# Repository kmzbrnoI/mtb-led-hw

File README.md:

MTB-LED PCB
===========

MTB-LED is a 32-output LED driver. It communicates over [MTBbus](https://mtb.kmz-brno.cz/bus) (RS485).
The module is designed for controlling street and house lights on model
railroad, however is could be used generally in any other application.

This repository contains schematics & PCB layout of MTB-LED PCB. Firmware
for main MCU ATmega328p is available
[here](https://github.com/kmzbrnoI/mtb-led-fw). More information about
MTB in available [here](https://mtb.kmz-brno.cz/).

## Design

Schematics & PCB are designed in KiCad 9.

## Production

PCB is prepared to be automatically assembled in [JLCPCB](https://jlcpcb.com/).
SMD parts on **bootom** side should be assembled. Each SMD part has its `LCSC`
attribute set.

```bash
$ make
```

## Parameters

 * Input voltage: 7–17 V.
   Protection: when > 18 V is applied, input is shorted. Afterwards, current
   is limited by PTC fuse on input to 200 mA. Reverse-polarity protection.
 * Max current consumption: ??? mA.
 * Outputs: 32 constant-current PWM-controlled outputs for LED connection. Connect
   positive pole of LED to power supply, negative to the MTB-LED module.

## Piece check

Following checks should be performed to mark each manufactured piece as *QC PASS*.

1. Check module communicates on MTBbus.
2. Check all LEDs are working.
3. Check button is working.
4. Calibrate `TS_OFFSET`, check diagnostic including temperature measurement is working.
5. Check all outputs are working.

## Authors

MTB-LED v4 module is designed by [Jan Malina](mailto:jan.malina@kmz-brno.cz),
[Model Railway Club Brno](https://www.kmz-brno.cz/).

## License

Content of the repository is provided under [Creative Commons
Attribution-ShareAlike 4.0
License](https://creativecommons.org/licenses/by-sa/4.0/) as openhardware
project. You may download any data, contribute to the project, create PCB
yourself or even sell it yourself.

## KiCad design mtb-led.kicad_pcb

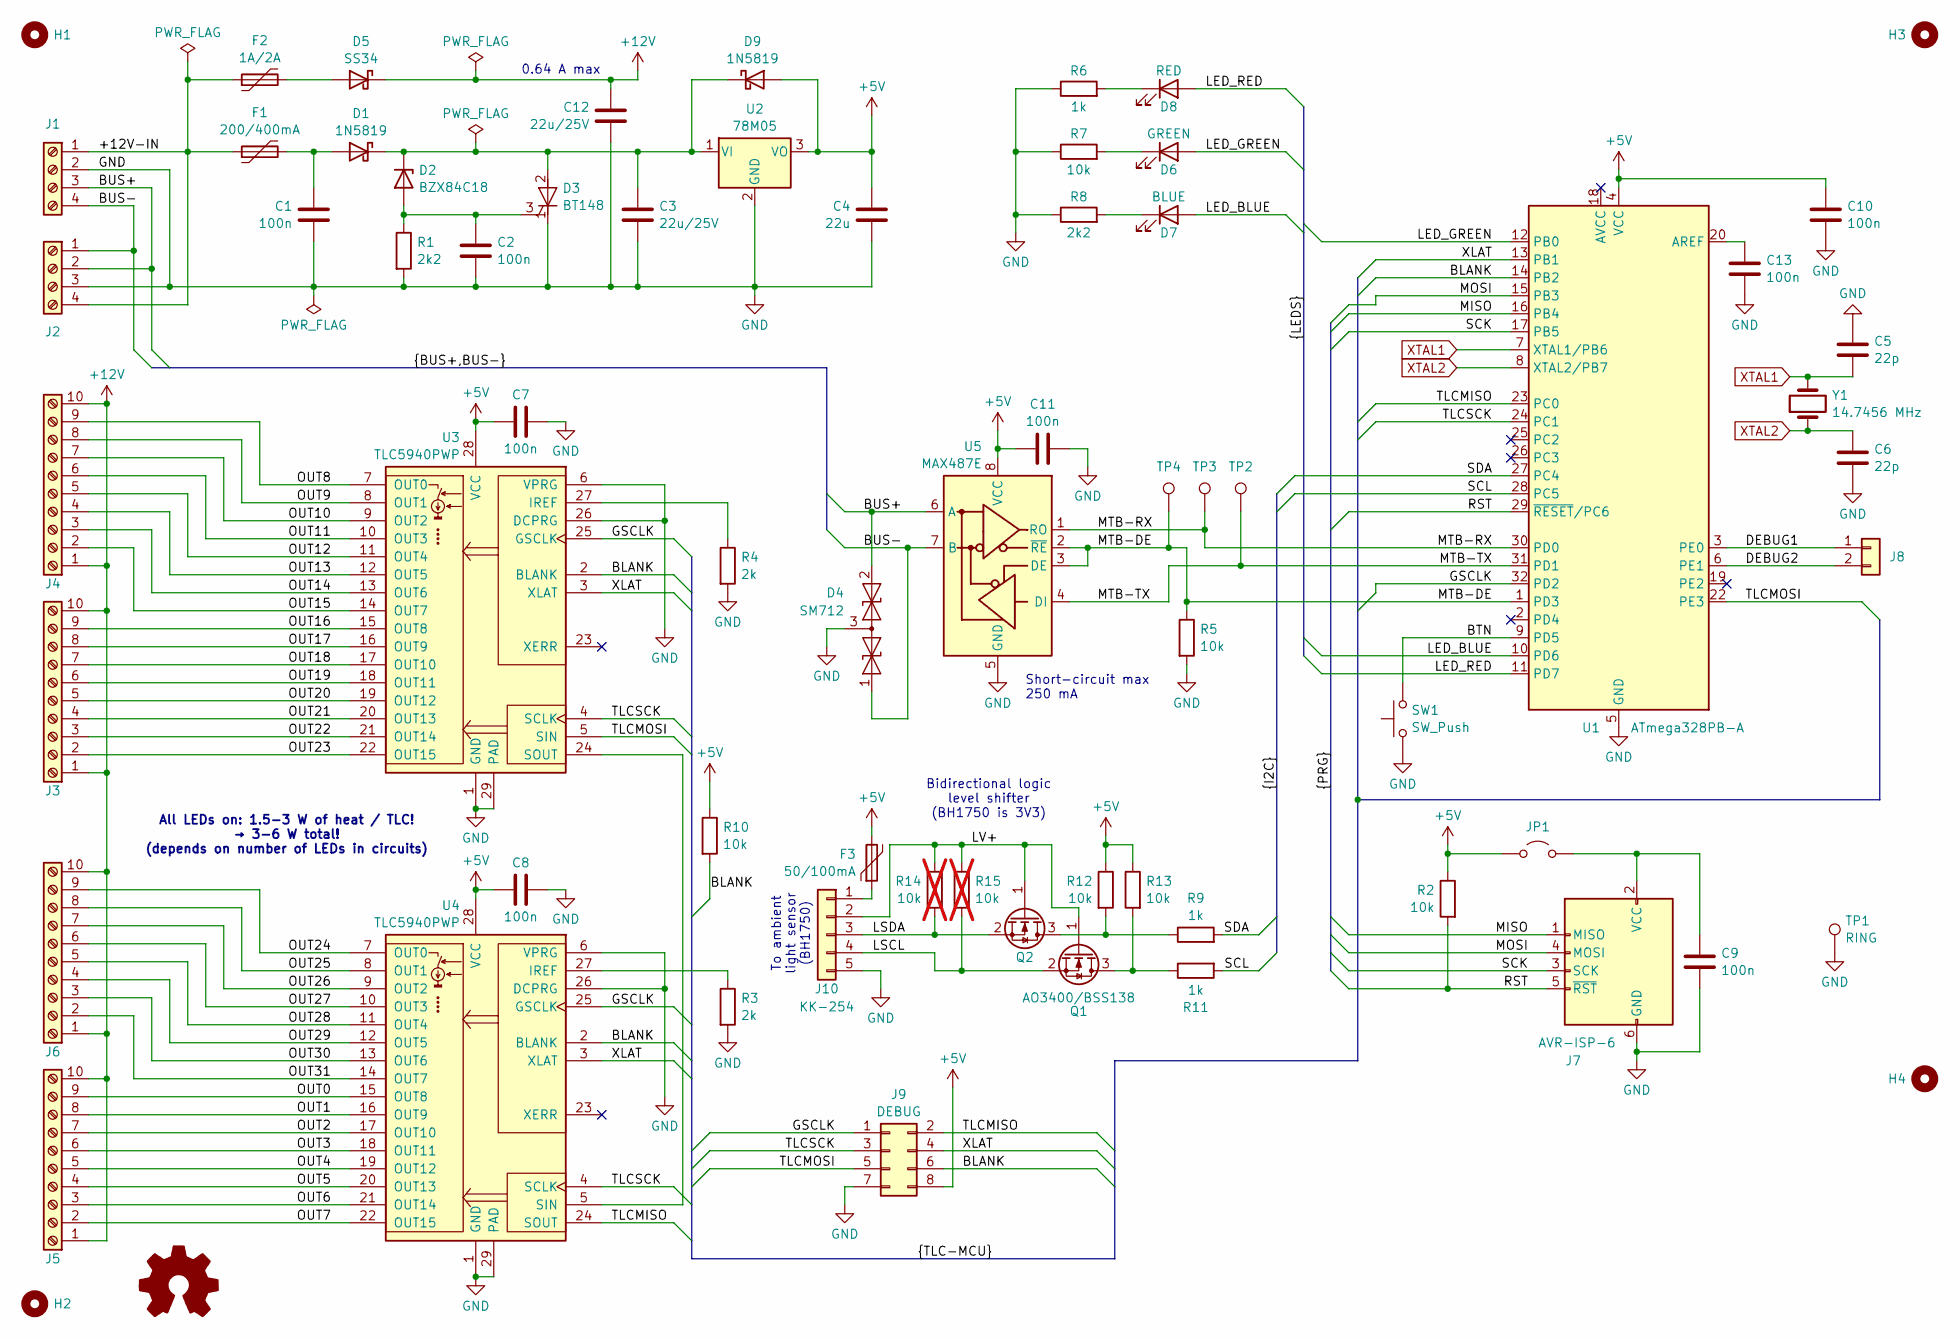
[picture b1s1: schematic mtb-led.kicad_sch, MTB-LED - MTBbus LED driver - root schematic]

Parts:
C1, C2, C7, C8, C9, C10, C11, C13: 100n; C_0805_2012Metric; LCSC C49678
C3, C12: 22u/25V; C_0805_2012Metric; LCSC C45783
C4: 22u; C_0805_2012Metric; LCSC C45783
C5, C6: 22p; C_0805_2012Metric; LCSC C1804
D1, D9: 1N5819; D_SOD-123; LCSC C191023
D2: BZX84C18; SOT-23; LCSC C896938
D3: BT148; SOT-223; LCSC C256433
D4: SM712; SOT-23; LCSC C2827658
D5: SS34; D_SMA; LCSC C8678
D6: GREEN; LED_0805_2012Metric; JLCPCB_IGNORE true
D7: BLUE; LED_0805_2012Metric; JLCPCB_IGNORE true
D8: RED; LED_0805_2012Metric; JLCPCB_IGNORE true
F1: 200/400mA; Fuse_1812_4532Metric_Pad1.30x3.40mm_HandSolder; JLCPCB_IGNORE true
F2: 1A/2A; Fuse_1812_4532Metric_Pad1.30x3.40mm_HandSolder; JLCPCB_IGNORE true
F3: 50/100mA; Fuse_1206_3216Metric; LCSC C2830235
H1, H2, H3, H4: MountingHole_3.2mm_M3_Pad_Via; JLCPCB_IGNORE true
J1, J2: PhoenixContact_MSTBA_2,5_4-G_1x04_P5.00mm_Horizontal; JLCPCB_IGNORE true
J3, J4, J5, J6: PhoenixContact_MC_1,5_10-G-3.5_1x10_P3.50mm_Horizontal; JLCPCB_IGNORE true
J7: AVR-ISP-6; PinHeader_2x03_P2.54mm_Vertical; JLCPCB_IGNORE true
J8: PinHeader_2x01_P2.54mm_Vertical; JLCPCB_IGNORE true
J9: DEBUG; PinHeader_2x04_P2.54mm_Vertical; JLCPCB_IGNORE true
J10: KK-254; Molex_KK-254_AE-6410-05A_1x05_P2.54mm_Vertical; JLCPCB_IGNORE true
JP1: PinHeader_2x01_P2.54mm_Vertical; JLCPCB_IGNORE true
Q1, Q2: AO3400/BSS138; SOT-23; LCSC C20917
R1, R8: 2k2; R_0805_2012Metric; LCSC C17520
R2, R5, R7, R10, R12, R13: 10k; R_0805_2012Metric; LCSC C17414
R3, R4: 2k; R_0805_2012Metric; LCSC C17604
R6, R9, R11: 1k; R_0805_2012Metric; LCSC C17513
R14, R15: 10k; R_0805_2012Metric; not fitted
SW1: SW_Push; SW_PUSH_6mm_H4.3mm; JLCPCB_IGNORE true
TP1: RING; TestPoint_Loop_D1.80mm_Drill1.0mm_Beaded; JLCPCB_IGNORE true
TP2, TP3, TP4: PinHeader_1x01_P2.54mm_Vertical; JLCPCB_IGNORE true
U1: ATmega328PB-A; TQFP-32_7x7mm_P0.8mm; LCSC C132230
U2: 78M05; TO-252-2; LCSC C58069
U3, U4: TLC5940PWP; HTSSOP-28-1EP_4.4x9.7mm_P0.65mm_EP3.4x9.5mm_Mask2.4x6.17mm_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; LCSC C181653
U5: MAX487E; DIP-8_W7.62mm_LongPads; JLCPCB_IGNORE true
Y1: 14.7456 MHz; Crystal_HC49-4H_Vertical; JLCPCB_IGNORE true

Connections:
+5V: C4.1, C7.1, C8.1, C10.1, C11.1, D9.2 (A), F3.2, J9.8, JP1.2 (B), R2.1, R10.1, R12.1, R13.1, U1.4 (VCC), U2.3 (VO), U3.28 (VCC), U4.28 (VCC), U5.8 (VCC)
+12V: C12.1, D5.1 (K), J3.1, J3.10, J4.1, J4.10, J5.1, J5.10, J6.1, J6.10
/+12V-IN: F1.1, F2.1, J1.1, J2.4
/BLANK: J9.6, R10.2, U1.14 (PB2), U3.2 (BLANK), U4.2 (BLANK)
/BTN: SW1.2, U1.9 (PD5)
/BUS+: D4.2 (A2), J1.3, J2.2, U5.6 (A)
/BUS-: D4.1 (A1), J1.4, J2.1, U5.7 (B)
/DEBUG1: J8.1, U1.3 (PE0)
/DEBUG2: J8.2, U1.6 (PE1)
/GSCLK: J9.1, U1.32 (PD2), U3.25 (GSCLK), U4.25 (GSCLK)
/LED_BLUE: D7.2 (A), U1.10 (PD6)
/LED_GREEN: D6.2 (A), U1.12 (PB0)
/LED_RED: D8.2 (A), U1.11 (PD7)
/LSCL: J10.4, Q1.2 (S), R15.2
/LSDA: J10.3, Q2.2 (S), R14.2
/LV+: J10.2, Q1.1 (G), Q2.1 (G), R14.1, R15.1
/MISO: J7.1 (MISO), U1.16 (PB4)
/MOSI: J7.4 (MOSI), U1.15 (PB3)
/MTB-DE: R5.1, TP4.1, U1.1 (PD3), U5.2 (~RE), U5.3 (DE)
/MTB-RX: TP3.1, U1.30 (PD0), U5.1 (RO)
/MTB-TX: TP2.1, U1.31 (PD1), U5.4 (DI)
/OUT0: J5.9, U4.15 (OUT8)
/OUT1: J5.8, U4.16 (OUT9)
/OUT2: J5.7, U4.17 (OUT10)
/OUT3: J5.6, U4.18 (OUT11)
/OUT4: J5.5, U4.19 (OUT12)
/OUT5: J5.4, U4.20 (OUT13)
/OUT6: J5.3, U4.21 (OUT14)
/OUT7: J5.2, U4.22 (OUT15)
/OUT8: J4.9, U3.7 (OUT0)
/OUT9: J4.8, U3.8 (OUT1)
/OUT10: J4.7, U3.9 (OUT2)
/OUT11: J4.6, U3.10 (OUT3)
/OUT12: J4.5, U3.11 (OUT4)
/OUT13: J4.4, U3.12 (OUT5)
/OUT14: J4.3, U3.13 (OUT6)
/OUT15: J4.2, U3.14 (OUT7)
/OUT16: J3.9, U3.15 (OUT8)
/OUT17: J3.8, U3.16 (OUT9)
/OUT18: J3.7, U3.17 (OUT10)
/OUT19: J3.6, U3.18 (OUT11)
/OUT20: J3.5, U3.19 (OUT12)
/OUT21: J3.4, U3.20 (OUT13)
/OUT22: J3.3, U3.21 (OUT14)
/OUT23: J3.2, U3.22 (OUT15)
/OUT24: J6.9, U4.7 (OUT0)
/OUT25: J6.8, U4.8 (OUT1)
/OUT26: J6.7, U4.9 (OUT2)
/OUT27: J6.6, U4.10 (OUT3)
/OUT28: J6.5, U4.11 (OUT4)
/OUT29: J6.4, U4.12 (OUT5)
/OUT30: J6.3, U4.13 (OUT6)
/OUT31: J6.2, U4.14 (OUT7)
/RST: J7.5 (~RST), R2.2, U1.29 (~RESET/PC6)
/SCK: J7.3 (SCK), U1.17 (PB5)
/SCL: R11.2, U1.28 (PC5)
/SDA: R9.2, U1.27 (PC4)
/TLCMISO: J9.2, U1.23 (PC0), U4.24 (SOUT)
/TLCMOSI: J9.5, U1.22 (PE3), U3.5 (SIN)
/TLCSCK: J9.3, U1.24 (PC1), U3.4 (SCLK), U4.4 (SCLK)
/XLAT: J9.4, U1.13 (PB1), U3.3 (XLAT), U4.3 (XLAT)
GND: C1.2, C2.2, C3.2, C4.2, C5.1, C6.2, C7.2, C8.2, C9.2, C10.2, C11.2, C12.2, C13.2, D3.1 (K), D4.3 (common), J1.2, J2.3, J7.6 (GND), J9.7, J10.5, R1.2, R3.2, R4.2, R5.2, R6.1, R7.1, R8.1, SW1.1, TP1.1, U1.5 (GND), U1.21 (GND), U2.2 (GND), U3.1 (GND), U3.6 (VPRG), U3.26 (DCPRG), U3.29 (PAD), U4.1 (GND), U4.6 (VPRG), U4.26 (DCPRG), U4.29 (PAD), U5.5 (GND)
unnamed: C1.1, D1.2 (A), F1.2
unnamed: C3.1, D1.1 (K), D2.3 (K), D3.2 (A), D9.1 (K), U2.1 (VI)
unnamed: C2.1, D2.1 (A), D3.3 (G), R1.1
unnamed: D5.2 (A), F2.2
unnamed: D6.1 (K), R7.2
unnamed: D7.1 (K), R8.2
unnamed: D8.1 (K), R6.2
unnamed: C9.1, J7.2 (VCC), JP1.1 (A)
unnamed: F3.1, J10.1
unnamed: Q1.3 (D), R11.1, R13.2
unnamed: Q2.3 (D), R9.1, R12.2
unnamed: C13.1, U1.20 (AREF)
unnamed: R4.1, U3.27 (IREF)
unnamed: U3.24 (SOUT), U4.5 (SIN)
unnamed: R3.1, U4.27 (IREF)
XTAL1: C5.2, U1.7 (XTAL1/PB6), Y1.2
XTAL2: C6.1, U1.8 (XTAL2/PB7), Y1.1

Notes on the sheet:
To ambient light sensor (BH1750)
Short-circuit max 250 mA
Bidirectional logic level shifter (BH1750 is 3V3)
All LEDs on: 1.5-3 W of heat / TLC! → 3-6 W total! (depends on number of LEDs in circuits)
0.64 A max

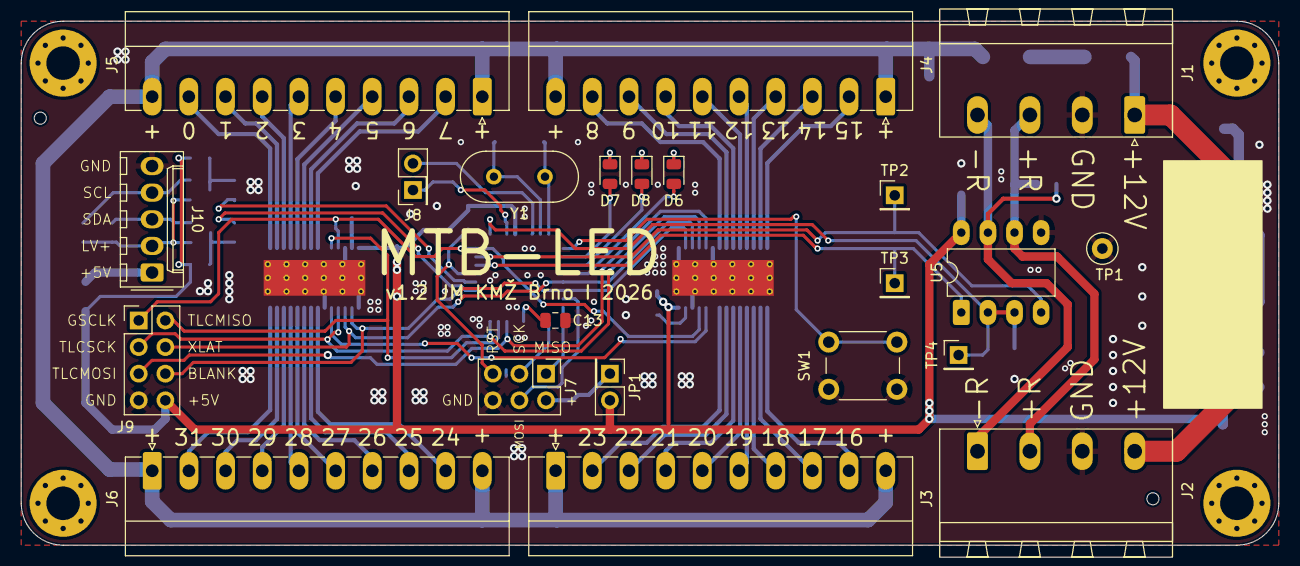
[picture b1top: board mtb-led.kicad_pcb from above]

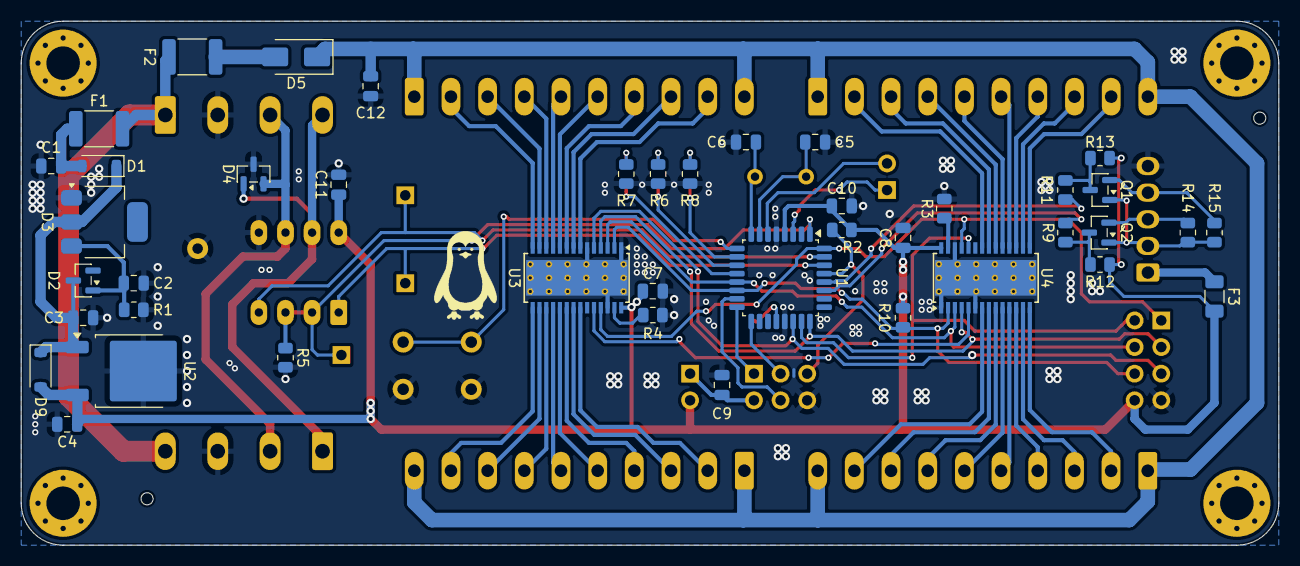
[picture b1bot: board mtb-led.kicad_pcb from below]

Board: 2 copper layers, 120.0 x 50.0 mm, 68 parts (42 on the bottom side), 79 nets.

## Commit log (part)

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2026-05-10 Add README, LICENSE, .gitignore.
2026-05-10 Add empty KiCad 9 project.
2026-05-10 Sch: add basic information.
2026-05-10 Sch: add basic parts, wire power supply.
2026-05-10 Sch: wire outputs.
2026-05-10 Sch: add MTBbus interface.
2026-05-10 Sch: connect TLS5940 and MCU.
2026-05-10 Add LEDs.
2026-05-10 Add debug pinheader.
2026-05-10 Set max LED current (20 ma), add more debug ifaces.
2026-05-11 Add DEBUG pinheader for mcu-tlc signals.
2026-05-11 Change output connectors 12->10 pin.
2026-05-11 Name output signals.
2026-05-14 Add VCC & GND to debug connector.
2026-05-14 Add footprints.
2026-05-14 Resolve ERC problems.
2026-05-14 PCB: add MTB-UNIsize pcb.
2026-05-14 PCB: basic placing of parts.
2026-05-14 PCB: wire, wire, ...
2026-05-14 Tweak silkscreen.
2026-05-14 PCB: add GND vias.
2026-05-14 Rename outputs according to PCB design.
2026-05-14 Add OSHW logo & web page url.
2026-05-15 Sch: minor movement.
2026-05-15 Add capacitor to +12V.
2026-05-15 PCB: add penguin.
2026-05-15 PCB: resolve serious DRC errors.
2026-05-15 Add JLCPCB tooling holes.
2026-05-16 Add JLCPCB part numbers.
2026-05-16 Add vias.
2026-06-14 Rewire MCU connection (v1.1).
    * Use OCR1A/B pins for XLAT & BLANK. HW timer output required.
    * Reconnect BLUE LED to different PIN.
    * Add MISO TLC->ATmega.
    * Use SPI1 for TLS connection, SPI0 for programming.
2026-06-14 Connect TLC5940 thermal pad to GND.
2026-06-17 PCB updates.
2026-06-17 Remove XERR signal.
    It is not used.
2026-06-17 Add AREF 100nF capacitor.
2026-06-17 Remove DCPG & VPRG signals MCU <-> TLC.
2026-06-18 Fix ERC & DRC issues.

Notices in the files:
mtb-led.kicad_sch:
Released under the Creative Commons Attribution-ShareAlike 4.0 License
